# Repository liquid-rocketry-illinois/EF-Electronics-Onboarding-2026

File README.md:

# LRI Electronics Onboarding 2026

Repository with onboarding code and speakernotes. Check the wiki tab at the top for instructions.

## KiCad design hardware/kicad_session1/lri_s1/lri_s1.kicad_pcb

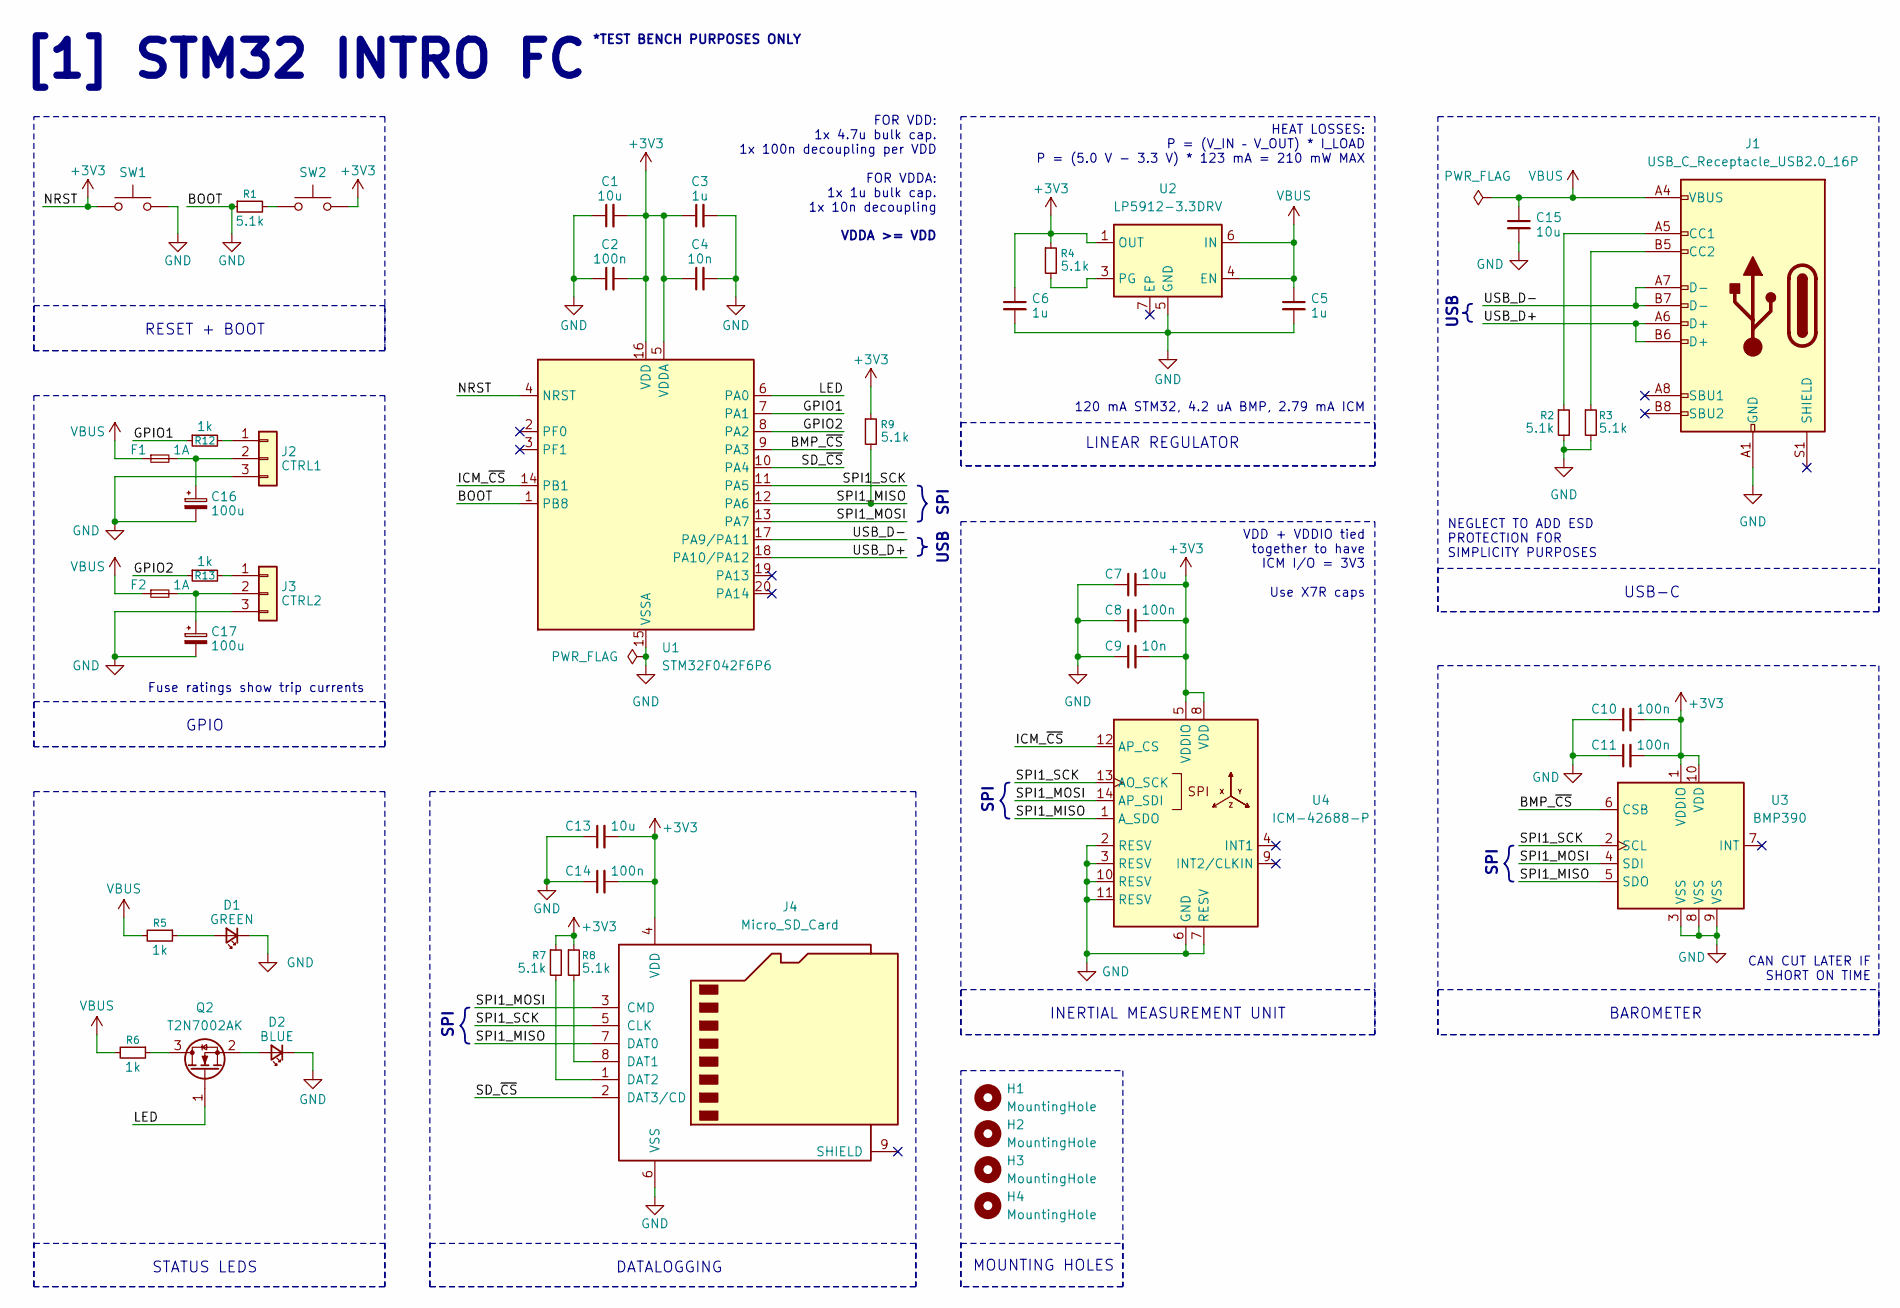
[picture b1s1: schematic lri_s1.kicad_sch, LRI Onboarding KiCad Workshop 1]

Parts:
C1, C7, C13, C15: 10u; C_0402_1005Metric
C2, C8, C10, C11, C14: 100n; C_0402_1005Metric
C3, C5, C6: 1u; C_0402_1005Metric
C4, C9: 10n; C_0402_1005Metric
C16, C17: 100u; CP_Radial_D5.0mm_P2.00mm
D1: GREEN; LED_0402_1005Metric
D2: BLUE; LED_0402_1005Metric
F1, F2: 1A; Fuse_0402_1005Metric
H1, H2, H3, H4: MountingHole; MountingHole_3.2mm_M3
J1: USB_C_Receptacle_USB2.0_16P; USB_C_Receptacle_GCT_USB4110
J2: CTRL1; PinSocket_1x03_P2.54mm_Vertical
J3: CTRL2; PinSocket_1x03_P2.54mm_Vertical
J4: Micro_SD_Card; microSD_HC_Molex_47219-2001
Q2: T2N7002AK; SOT-23
R1, R2, R3, R4, R7, R8, R9: 5.1k; R_0402_1005Metric
R5, R6, R12, R13: 1k; R_0402_1005Metric
SW1, SW2: SW_Push; SW_SPST_PTS810
U1: STM32F042F6P6; TSSOP-20_4.4x6.5mm_P0.65mm
U2: LP5912-3.3DRV; WSON-6-1EP_2x2mm_P0.65mm_EP1x1.6mm_ThermalVias
U3: BMP390; BMP390_LGA_2x2x0.75; MPN BMP390
U4: ICM-42688-P; ICM-42688_LGA_0.91x2.50x3.00; MPN ICM-42688-P

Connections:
+3V3: C1.2, C2.2, C3.1, C4.1, C6.1, C7.2, C8.2, C9.2, C10.2, C11.2, C13.2, C14.2, J4.4 (VDD), R4.1, R7.1, R8.1, R9.1, SW1.1, SW2.2, U1.4 (NRST), U1.5 (VDDA), U1.16 (VDD), U2.1 (OUT), U3.1 (VDDIO), U3.10 (VDD), U4.5 (VDDIO), U4.8 (VDD)
/BMP_~CS: U1.9 (PA3), U3.6 (CSB)
/GPIO1: R12.1, U1.7 (PA1)
/GPIO2: R13.1, U1.8 (PA2)
/ICM_~CS: U1.14 (PB1), U4.12 (AP_CS)
/LED: Q2.1 (G), U1.6 (PA0)
/SD_~CS: J4.2 (DAT3/CD), U1.10 (PA4)
/SPI1_MISO: J4.7 (DAT0), R9.2, U1.12 (PA6), U3.5 (SDO), U4.1 (A_SDO)
/SPI1_MOSI: J4.3 (CMD), U1.13 (PA7), U3.4 (SDI), U4.14 (AP_SDI)
/SPI1_SCK: J4.5 (CLK), U1.11 (PA5), U3.2 (SCL), U4.13 (AO_SCK)
/USB_D+: J1.A6 (D+), J1.B6 (D+), U1.18 (PA10/PA12)
/USB_D-: J1.A7 (D-), J1.B7 (D-), U1.17 (PA9/PA11)
GND: C1.1, C2.1, C3.2, C4.2, C5.2, C6.2, C7.1, C8.1, C9.1, C10.1, C11.1, C13.1, C14.1, C15.2, C16.2, C17.2, D1.1 (K), D2.1 (K), J1.A1 (GND), J1.A12 (GND), J1.B1 (GND), J1.B12 (GND), J2.3, J3.3, J4.6 (VSS), R1.1, R2.2, R3.2, SW1.2, U1.1 (PB8), U1.15 (VSSA), U2.5 (GND), U3.3 (VSS), U3.8 (VSS), U3.9 (VSS), U4.2 (RESV), U4.3 (RESV), U4.6 (GND), U4.7 (RESV), U4.10 (RESV), U4.11 (RESV)
unnamed: D1.2 (A), R5.1
unnamed: D2.2 (A), Q2.2 (S)
unnamed: J1.A5 (CC1), R2.1
unnamed: J1.B5 (CC2), R3.1
unnamed: J2.1, R12.2
unnamed: C16.1, F1.2, J2.2
unnamed: J3.1, R13.2
unnamed: C17.1, F2.2, J3.2
unnamed: J4.8 (DAT1), R8.2
unnamed: J4.1 (DAT2), R7.2
unnamed: Q2.3 (D), R6.1
unnamed: R1.2, SW2.1
unnamed: R4.2, U2.3 (PG)
VBUS: C5.1, C15.1, F1.1, F2.1, J1.A4 (VBUS), J1.A9 (VBUS), J1.B4 (VBUS), J1.B9 (VBUS), R5.2, R6.2, U2.4 (EN), U2.6 (IN)

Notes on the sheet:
SPI
CAN CUT LATER IF SHORT ON TIME
VDD + VDDIO tied together to have ICM I/O = 3V3 Use X7R caps
RESET + BOOT
USB
GPIO
[1] STM32 INTRO FC
VDDA >= VDD
HEAT LOSSES: P = (V_IN – V_OUT) * I_LOAD P = (5.0 V - 3.3 V) * 123 mA = 210 mW MAX
STATUS LEDS
INERTIAL MEASUREMENT UNIT
LINEAR REGULATOR
FOR VDD: 1x 4.7u bulk cap. 1x 100n decoupling per VDD FOR VDDA: 1x 1u bulk cap. 1x 10n decoupling
120 mA STM32, 4.2 uA BMP, 2.79 mA ICM
NEGLECT TO ADD ESD PROTECTION FOR SIMPLICITY PURPOSES
MOUNTING HOLES
*TEST BENCH PURPOSES ONLY
USB-C
DATALOGGING
Fuse ratings show trip currents
BAROMETER

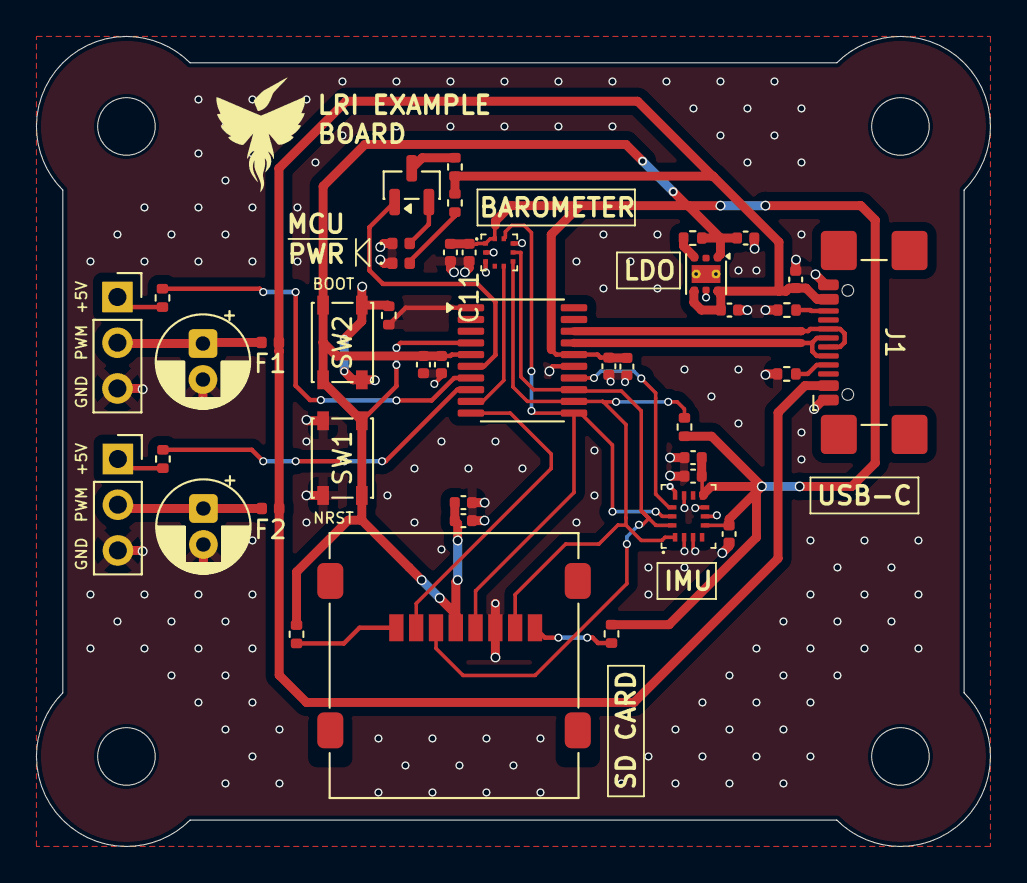
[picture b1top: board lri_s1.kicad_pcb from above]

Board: 2 copper layers, 53.0 x 45.0 mm, 46 parts (0 on the bottom side), 27 nets.

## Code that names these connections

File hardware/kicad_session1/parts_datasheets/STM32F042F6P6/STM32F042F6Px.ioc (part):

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Mcu.Name=STM32F042F6Px
Mcu.Package=TSSOP20
Mcu.UserName=STM32F042F6Px
PA0.Signal=GPIO_Output
PA1.Signal=S_TIM2_CH2
PA13.Signal=GPIO_Output
PA14.Signal=GPIO_Output
PA2.Signal=S_TIM2_CH3
PA3.Signal=GPIO_Output
PA4.Signal=GPIO_Output
PA5.Mode=Full_Duplex_Master
PA5.Signal=SPI1_SCK
PA6.Mode=Full_Duplex_Master
PA6.Signal=SPI1_MISO
PA7.Mode=Full_Duplex_Master
PA7.Signal=SPI1_MOSI
PB1.Signal=GPIO_Output
PB8.Signal=GPIO_Output
board=custom
